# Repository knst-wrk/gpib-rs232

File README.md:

# GPIB-RS232 Converter

This circuit interfaces a GPIB bus to a serial port.

It was originally published on the German website [Mikrocontroller.net](https://www.mikrocontroller.net/articles/GPIB-RS232-Schnittstelle) and [featured on Hackaday](https://hackaday.com/2012/05/01/gpib-connectivity-twofer/).

## License and state

Software is GPL-3.0 unless otherwise noted.

The circuit design is licensed under the CERN OHL-W-2.0.

The project has been sitting around for some time now. I would consider it to be mildly abandoned by now as I currently do not have the time and/or energy to continue working on it, unfortunately. Please feel free to send me a mail if you have questions or suggestions or if you can make use of it.

## GPIB-RS232-Schnittstelle

Viele Messgeräte sind (auch heute immer noch) mit einer GPIB-Schnittstelle ausgerüstet. Zwar handelt es sich hierbei zwar um einen eher antiquierten, parallelen Datenbus, den Hewlett-Packard vor nunmehr vierzig Jahren in die Welt gesetzt hat, dennoch sind es vor allem die [geringen Übertragungslatenzen](https://www.ni.com/en/support/downloads/instrument-drivers/instrument-bus-performance---making-sense-of-competing-bus-techn.html#vergleichsweise), welche die GPIB-Schnittstelle auch weiterhin für zeitkritische Aufgaben prädestinieren. Mittlerweile wurde die GPIB-Schnittstelle vielfach genormt - unter anderem unter der Bezeichnung IEEE488 und IEC-625, daher auch die gängige Bezeichnung als *IEC-BUS*.

Der Bus ist acht Bit breit und beinhaltet neben einer Reihe von Steuerleitungen ein Drei-Leitungs-Handshake. Dieses ist in Wired-And-Methodik ausgeführt, d.h. der Bus wird terminiert und mit Pull-up versehen, welchen die Busteilnehmer dann aktiv nach Masse ziehen können. Das Handshake gewährleistet, dass der Bus nur so schnell betrieben wird, wie das langsamste Gerät am Bus Daten aufnehmen kann. Der genaue Ablauf des Bustransfers ist in dieser Grafik recht anschaulich beschrieben.

Funktionen:
* GPIB-Controller, also SH, AH, C,
* HP Universal Language Interface auf der seriellen,
* Zustandsanzeige über Blinkmuster...,
* Vernünftige Pegelwandler und keine Spannungsteiler,
* umfangreiche End-of-string-Behandlung.

## Terminologie
Sämtliche Signale auf dem Bus sind Low-aktiv.

Der Bus besteht aus den acht Datenleitungen des Datenbus, die das Datenbyte aufnehmen (invertiert, da Low-aktiv). Ein Byte kann *auf den Bus gelegt werden*, indem die Treiber eingeschaltet werden und die Datenleitungen entsprechend gesetzt werden. Um das Byte wieder *vom Bus zu nehmen*, werden die Treiber wieder abgeschaltet. Das ist etwas anderes, als ein Byte *vom Bus zu lesen*!

Dazu kommt der Übergabebus mit den drei Handshakeleitungen DAV (data available), NDAC (no data accepted) und NRFD (not ready for data). Schließlich bilden ein paar Steuerleitungen den Steuerbus; die wichtigsten wären
* ATN (attention),
* REN (remote enable) und
* EOI (end or identify).

Man spricht beim GPIB eigentlich immer von irgendwelchen *Botschaften*, die abgesetzt oder zurückgezogen werden. Es kann sich dabei um Bytes handeln, die über den Bus gehen, oder auch schlicht um eine der Steuer- oder Handshakeleitungen, die einen bestimmten Pegel annimmt. Da der Bus Low-aktiv arbeitet, sind insbesondere die Steuerleitungen aktiv, wenn sie einen niedrigen Spannungspegel annehmen. Die entsprechende Botschaft ist dann *gesendet* (oder *abgesetzt*). Wegen Wired-and können auch mehrere Busteilnehmer eine Botschaft zugleich absetzen. Sie bleibt dann solange abgesetzt, bis sämtliche Teilnehmer sie wieder *zurückgezogen* haben.

Mit der DAV-Botschaft (data valid) wird signalisiert, dass der Datenbus gültige Daten enthält, die nun gelesen werden können. Wird die EOI-Botschaft (end or identify) zusammen mit einem Byte übertragen, so handelt es sich um das letzte Byte einer längeren Nachricht. Die ATN-Botschaft (attention) fordert alle Busteilnehmer auf, sämtliche Bustätigkeit zu unterbrechen und den Datenbus freizugeben (etwaige Talker nehmen ihr Byte vom Bus).

## Hardware
Die Schnittstelle wurde vollständig in bedrahteter Technologie auf einer einseitigen Platine aufgebaut. Für die serielle Schnittstelle kommt der MAX232 zum Einsatz, die Busankopplung nehmen die klassichen SN75160 (Daten) und SN75162 (Steuerleitungen). Zusammengehalten wird beides von einem ATmega16 oder pinkompatiblen. Die Bustreiber sind eigentlich typisch; den -160 bekommt man bei Reichelt. Den zweiten gibt es dort noch als -161; dem fehlen allerdings zwei wichtige Signale, es muss also der -162 sein.

Notfalls lassen sich die Treiber auch aus alten GPIB-Karten ausschlachten...

Zuletzt habe ich noch ein geregeltes Netzteil (7805) spendiert, um die Karte über Hohlstecker zu versorgen. Man halte sich dabei die vergleichsweise große Verlustleistung der Bustreiber vor Augen, wenn man mit dem Gedanken spielt, die Karte über USB zu versorgen: Im Leerlauf insgesamt etwa 150mA.

Zum Bus hin habe ich den typischen Centronics-Stecker (*micro ribbon connector*) verbaut. Da ist etwas Vorsicht geboten, denn die gibt es auch in gespiegelter Bauform. Der Stecker ist trapezförmig; die normale Bauform hat das schmale Ende unten (Richtung Platine), die gespiegelte Version nach oben. Ich habe die normale Version gewählt.

Es gibt auf der Platine keine diskrete Logik für die ATN-Leitung. Das mag mancheinem vielleicht schon aufgefallen sein, der alte GPIB-PCI-Steckkarten gesehen hat -- die glichen anfangs einem TTL-Grab. Hintergrund ist, dass in der Spezifikation ein recht zeitkritisches Verhalten als Antwort auf die ATN-Botschaft vereinbart ist. Nämlich haben alle Busteilnehmer bei Empfang der ATN-Botschaft ihren Busbetrieb binnen 200ns einzustellen und die Treiber zu deaktivieren.

Das Zeitfenster von 200ns ist recht sportlich, um es mit einem Interrupt aufzufangen, gerade bei den alten Mikroprozessors, die auf den Steckkarten verbaut wurden, und auch für den AVR. Daher hat man diese Spezifikation (und noch ein paar weitere) mit diskreter Logik erschlagen. Diese hat sich dann schnell um die Bustreiber gekümmert und einfach ein Flipflop gesetzt. Dieses hat der Mikroprozessor dann bei nächster Gelegenheit abgeholt und hatte damit wieder genug Zeit, zu reagieren.

## Software
Die Software ist in C für avr-gcc geschrieben.

### Controller-Betrieb
Die fehlende diskrete Logik hat zur Konsequenz, dass die Schnittstelle eigentlich nur als Controller standardkonform funktioniert. Denn nur dann kümmert sie sich selbst um die ATN-Botschaft und muss demnach nicht auf fremde ATN-Botschaften reagieren, was sie ja aus Zeitgründen nicht innerhalb des spezifizierten Zeitfensters kann. Würde man die Schnittstelle nur als Sprecher (Talker) betreiben, könnte der momentane Controller die ATN-Botschaft versenden und gleich darauf ein paar Daten auf den Bus legen. Tut er das so schnell wie möglich, also nach 200ns, hätte die Schnittstelle keine Chance, etwaige Daten vom Bus zu nehmen, denn mit zwei Prozessorzyklen des AVR (bei 8MHz) wären die 200ns schon beim Sprung in den Interrupt verstrichen (rjmp mit zwei Zyklen = 250ns). Und da sind noch nicht die vier Takte drin, die bis zum Interruptvektor vergehen, denn es muss ja noch der Programmzähler auf den Stack gelegt werden.

Praktisch ist der Bus in Wired-and ausgeführt, d.h. es entstehen zumindest keine Kurzschlüsse, wenn zwei gleichzeitig reden, weil die Treiber nicht schnell genug abgeschaltet werden. Es können aber Daten kaputt gehen, wenn andere Teilnehmer die Daten früher vom Bus lesen, als jemand anderes seine Treiber abschaltet. Und zwar nach folgendem Szenario:

* Wir legen ein Byte auf den Bus und
* signalisieren das mit der DAV-Botschaft.
* Ein paar Hörer lesen das Byte vom Bus.
* Der Controller setzt die ATN-Botschaft ab,
* er wartet die 200ns und
* legt seinerseits ein Byte auf den Bus (dieses kollidiert mit unserem) und
* signalisiert das mit der DAV-Botschaft. Die DAV-Botschaft bleibt also bestehen (Wired-and).
* Ein paar andere Hörer lesen das (kaputte) Byte vom Bus.
* Wir bemerken die ATN-Botschaft und ziehen Byte und ATN-Botschaft zurück.
* Wegen Wired-and ist die DAV-Botschaft noch immer aktiv.
* ...

Der Betrieb als Hörer leidet am gleichen Problem, hier ist allerdings das Lesen vom Bus kritisch. Ein Sprecher könnte ein Datenbyte auf den Bus legen und dies mit der DAV-Botschaft signalisieren. Das bemerken wir und beginnen mit dem Lesevorgang (Interrupt betreten und so weiter). Indes unterbricht ein Controller die Übertragung mit der ATN-Botschaft der Bus enthält dann ungültige Daten. Und wir fahren munter mit dem begonnenen Lesevorgang fort...

Unterm Strich: Meistens funktioniert es.

### Protokoll
Für das Protokoll über die serielle Schnittstelle habe ich mich vom Universal Language Interface (ULI) von Hewlett-Packard inspirieren lassen. Das Heftchen von 1993 fiel mir zufällig in die Hände und ich fand das ganz passend.

Das Prinzip dahinter ist recht einfach. Früher hat man eine GPIB-Karte in den Computer gesteckt und bekam einen Treiber für ein recht bekanntes Betriebssystem seiner Zeit. Dazu kamen ein paar Bibliotheken für BASIC, C, Pascal und so weiter, die entsprechende Funktionen boten. Dazu gehörten Lese- und Schreibbefehle `ibrd()` und `ibwr()`, Funktionen zur Adressiereung und allerlei Zubehör. Je nach Hersteller waren diese Funktionen dann mehr oder weniger ähnlich und/oder inkompatibel.

Beim ULI dagegen erzeugte der Treiber quasi eine Gerätedatei, die man in der jeweiligen Programmiersprache dann mit Standard-E/A öffnen konnte. Das entspricht in etwa dem, was sich unter *nix schon länger bewährt hat. Eine Bibliothek gibt es nicht mehr, stattdessen werden Befehle zeilenweise in dieses Gerät geschrieben und Antworten kommen zeilenweise wieder heraus.

Zeilenweise ist in diesem Zusammenhang schwierig. Einerseits könnten Zeilenendzeichen (Wagenrücklauf CR, Zeilenvorschub LF) auch im Nutzdatenstrom vorkommen, andererseits konstruierte sich anfangs jeder Hersteller von GPIB-Messgeräten ein eigenes Bild vom Zeilenende. Manche wollten nur ein CR oder LF, manche CRLF, ein Semikolon oder die EOI-Botschaft (die EOI-Steuerleitung kann zusammen mit dem letzten übertragenen Byte gesetzt werden und signalisiert dann das Zeilenende). Glücklicherweise waren und sind die meisten Geräte recht tolerant und akzeptieren eine Vielzahl dieser Möglichkeiten, wenn man mit ihnen spricht. Tragischerweise antworten sie aber auch mit einer Vielzahl dieser Möglichkeiten, wenn sie umgekehrt mit uns sprechen...

### Architektur
Die Firmware ist mehrschichtig konstruiert. Ganz unten liegen zwei Ringpuffer, einer für die serielle Schnittstelle und einer für den GPIB. Diese Puffer kümmern sich um die Handshakes (Dreileitung für GPIB und RTS/CTS für die serielle).

Darüber liegt eine Strom-Schicht (Strom von Datenstrom), die aus den eingehenden Datenströmen der Ringpuffer die Zeilenenden herausfischt und die Zeilenenden in den ausgehenden Strömen erzeugt. Von da an sind beide Schnittstellen an die C-Laufzeitbibliothek angeschlossen, sodass die Kommunikation in weiten Teilen wie gewohnt mit `puts()`/`printf()`/... abläuft. Die Zeilenenden in den Eingangsströmen werden dabei als End-of-file (EOF) dargestellt. Da man allerdings kein EOF in den Ausgangsströmen erzeugen kann (könnte man schon, mit `fclose()`; diese Funktion ist aber schon anderweitig vergeben), werden die Zeilenenden mit einem flush ausgelöst. Blöderweise ist auch `fflush()` schon vergeben, daher zwei spezifische Routinen.

Obenauf liegt ein Terminal und verbindet die beiden Schnittstellen über das ULI.

### Beispiel
Eine Sitzung mit dem Universalzähler *PM6652* und dem Generator *PM5192* könnte etwa so aussehen:

Die Baudrate wird automatisch am ersten empfangenen Zeilenvorschub ermittelt:

    $ echo > ttyUSB1

Schnittstelle einschalten und den Zähler (Adresse 14) parametrieren:

    $ echo "ONLINE" > ttyUSB1
    $ echo "REMOTE 14" > ttyUSB1
    $ echo "OUTPUT 14;D" > ttyUSB1
    $ echo "OUTPUT;F1TE1G0SM5" > ttyUSB1

Zähler auf 1337Hz einstellen:

    $ echo "REMOTE 15" > ttyUSB1
    $ echo "OUTPUT 15;OUT 15;WSLA4F1337" > ttyUSB1

Messung durchführen und Ergebnis abholen:

    $ echo "TRIGGER 14" > ttyUSB1
    $ echo "ENTER 14" > ttyUSB1
    $ line < ttyUSB1
    FA 001.3370011E+3

Die Anführungszeichen sind nötig, damit die Shell das Semikolon nicht als Befehlsende interpretiert.

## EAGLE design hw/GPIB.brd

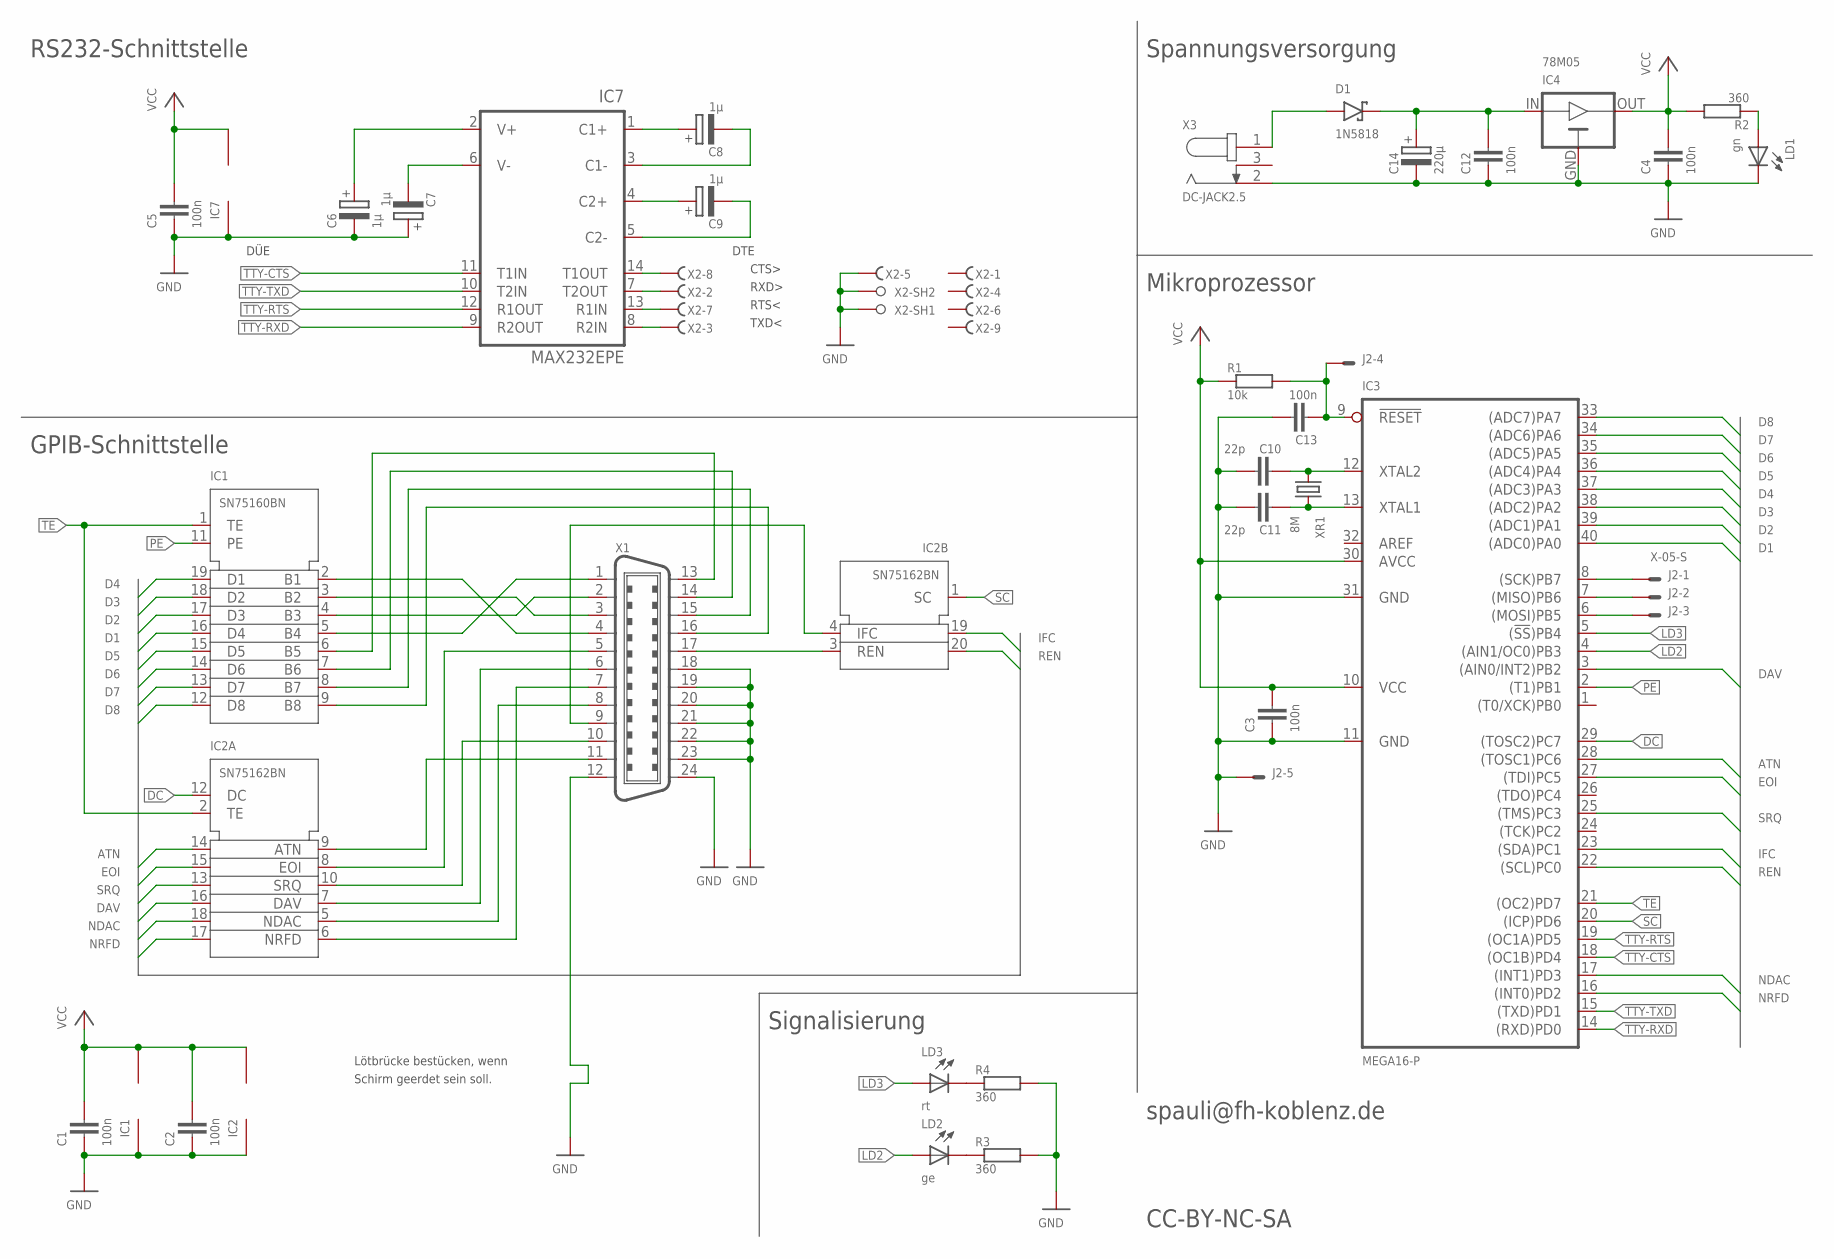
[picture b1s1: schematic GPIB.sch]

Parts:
C1, C2, C3, C4, C5, C12, C13: 100n; 024X044/020
C6, C7, C8, C9: 1µ; POL-D040/008
C10, C11: 22p; 024X044/010
C14: 220µ; POL-D080/014
D1: 1N5818; DO41/40
IC1: SN75160BN; DIL20
IC2: SN75162BN; DIL22-04
IC3: MEGA16-P; DIL40
IC4: 78M05; 78*-TO220-L
IC7: MAX232EPE; DIL16
J2: X-05-S; 05/4X010-S
LD1: gn; LED3MM
LD2: ge; LED3MM
LD3: rt; LED3MM
R1: 10k; 0204/030
R2, R3, R4: 360; 0204/030
X1: C24H; 24H
X2: 09F; F09HP
X3: DC-JACK2.5; DC-2.5
XR1: 8M; HC49-S

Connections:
!RESET: C13.2, IC3.9 (!RESET), J2.4, R1.2
ATN: IC2.14 (ATN_), IC3.28 ((TOSC1)PC6)
D1: IC1.16 (D4), IC3.40 ((ADC0)PA0)
D2: IC1.17 (D3), IC3.39 ((ADC1)PA1)
D3: IC1.18 (D2), IC3.38 ((ADC2)PA2)
D4: IC1.19 (D1), IC3.37 ((ADC3)PA3)
D5: IC1.15 (D5), IC3.36 ((ADC4)PA4)
D6: IC1.14 (D6), IC3.35 ((ADC5)PA5)
D7: IC1.13 (D7), IC3.34 ((ADC6)PA6)
D8: IC1.12 (D8), IC3.33 ((ADC7)PA7)
DAV: IC2.16 (DAV_), IC3.3 ((AIN0/INT2)PB2)
DC: IC2.12 (DC), IC3.29 ((TOSC2)PC7)
EOI: IC2.15 (EOI_), IC3.27 ((TDI)PC5)
GND: C1.2, C2.2, C3.2, C4.2, C5.2, C6.-, C7.+, C10.1, C11.1, C12.2, C13.1, C14.-, IC1.10 (GND), IC2.11 (GND), IC3.11 (GND), IC3.31 (GND), IC4.GND, IC7.15 (GND), J2.5, LD1.K (C), R3.2, R4.2, X1.12, X1.18, X1.19, X1.20, X1.21, X1.22, X1.23, X1.24, X2.5 (F), X2.SH1 (-SH), X2.SH2 (-SH), X3.2 (GROUND)
IFC: IC2.19 (IFC_), IC3.23 ((SDA)PC1)
LD2: IC3.4 ((AIN1/OC0)PB3), LD2.A
LD3: IC3.5 ((!SS!)PB4), LD3.A
MISO: IC3.7 ((MISO)PB6), J2.2
MOSI: IC3.6 ((MOSI)PB5), J2.3
unnamed: C8.+, IC7.1 (C1+)
unnamed: C9.+, IC7.4 (C2+)
unnamed: C9.-, IC7.5 (C2-)
unnamed: C8.-, IC7.3 (C1-)
unnamed: C6.+, IC7.2 (V+)
unnamed: IC1.2 (B1), X1.4
unnamed: C7.-, IC7.6 (V-)
unnamed: IC1.3 (B2), X1.3
unnamed: IC1.4 (B3), X1.2
unnamed: IC1.5 (B4), X1.1
unnamed: IC1.6 (B5), X1.13
unnamed: IC1.7 (B6), X1.14
unnamed: IC1.8 (B7), X1.15
unnamed: IC1.9 (B8), X1.16
unnamed: IC2.8 (EOI), X1.5
unnamed: IC2.7 (DAV), X1.6
unnamed: IC2.6 (NRFD), X1.7
unnamed: IC2.5 (NDAC), X1.8
unnamed: IC2.10 (SRQ), X1.10
unnamed: IC2.9 (ATN), X1.11
unnamed: IC2.3 (REN), X1.17
unnamed: IC2.4 (IFC), X1.9
unnamed: C10.2, IC3.12 (XTAL2), XR1.1
unnamed: C11.2, IC3.13 (XTAL1), XR1.2
unnamed: D1.A, X3.1 (LIVE)
unnamed: C12.1, C14.+, D1.C, IC4.IN
unnamed: LD1.A, R2.1
unnamed: LD3.K (C), R4.1
unnamed: LD2.K (C), R3.1
unnamed: IC7.8 (R2IN), X2.3 (F)
unnamed: IC7.13 (R1IN), X2.7 (F)
unnamed: IC7.14 (T1OUT), X2.8 (F)
unnamed: IC7.7 (T2OUT), X2.2 (F)
NDAC: IC2.18 (NDAC_), IC3.17 ((INT1)PD3)
NRFD: IC2.17 (NRFD_), IC3.16 ((INT0)PD2)
PE: IC1.11 (PE), IC3.2 ((T1)PB1)
REN: IC2.20 (REN_), IC3.22 ((SCL)PC0)
SC: IC2.1 (SC), IC3.20 ((ICP)PD6)
SCK: IC3.8 ((SCK)PB7), J2.1
SRQ: IC2.13 (SRQ_), IC3.25 ((TMS)PC3)
TE: IC1.1 (TE), IC2.2 (TE), IC3.21 ((OC2)PD7)
TTY-CTS: IC3.18 ((OC1B)PD4), IC7.11 (T1IN)
TTY-RTS: IC3.19 ((OC1A)PD5), IC7.12 (R1OUT)
TTY-RXD: IC3.14 ((RXD)PD0), IC7.9 (R2OUT)
TTY-TXD: IC3.15 ((TXD)PD1), IC7.10 (T2IN)
VCC: C1.1, C2.1, C3.1, C4.1, C5.1, IC1.20 (VCC), IC2.22 (VCC), IC3.10 (VCC), IC3.30 (AVCC), IC4.OUT, IC7.16 (VCC), R1.1, R2.2

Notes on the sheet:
RS232-Schnittstelle
TXD<
RTS<
RXD>
CTS>
DTE
DÜE
GPIB-Schnittstelle
Spannungsversorgung
Lötbrücke bestücken, wenn
Schirm geerdet sein soll.
Mikroprozessor
spauli@fh-koblenz.de
Signalisierung
CC-BY-NC-SA

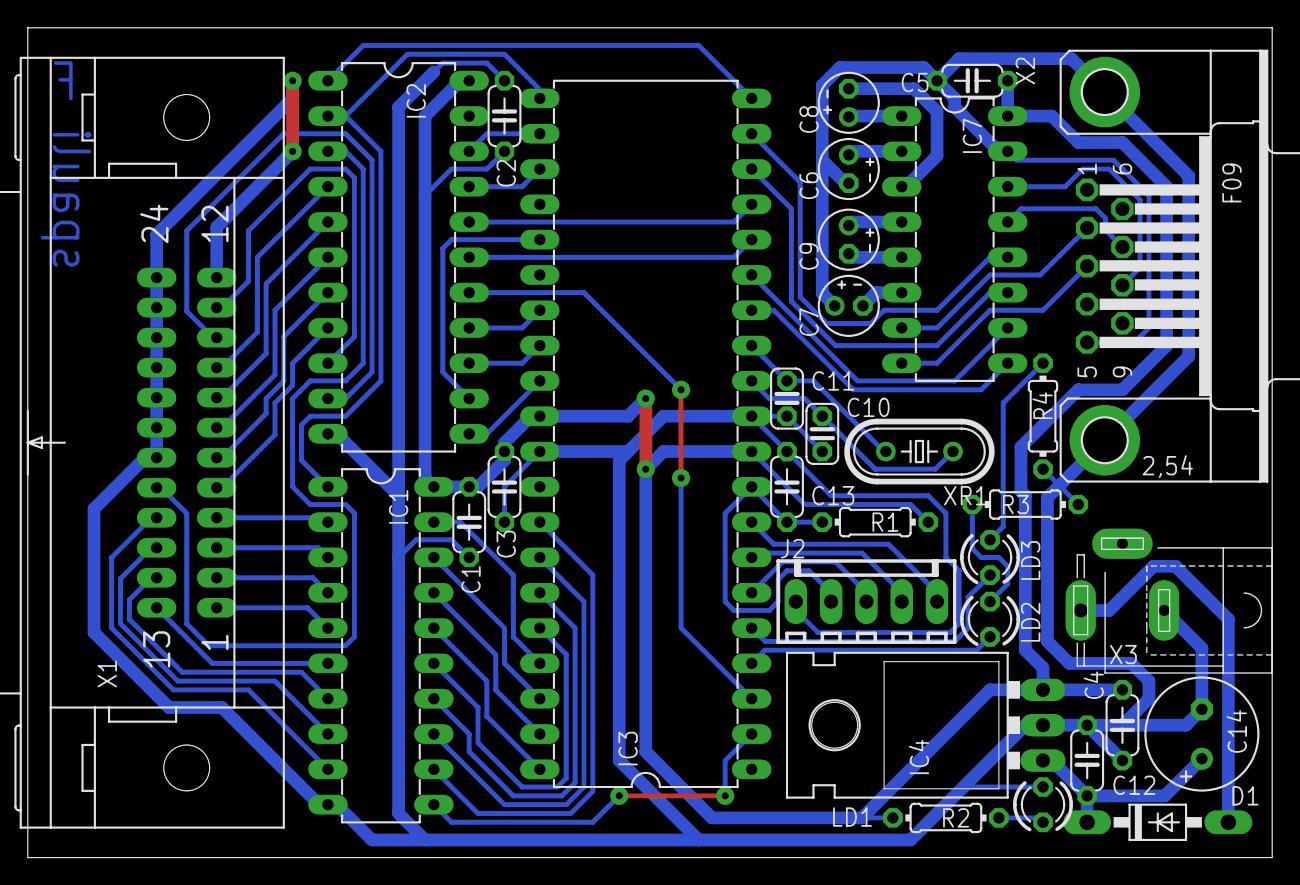
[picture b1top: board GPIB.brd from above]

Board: 2 copper layers, 89.5 x 59.7 mm, 32 parts (0 on the bottom side), 65 nets.

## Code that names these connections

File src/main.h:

/* GPIB to RS232 converter.
Copyright (C) 2012  Sven Pauli <sven_pauli@gmx.de>

This program is free software: you can redistribute it and/or
modify it under the terms of the GNU General Public License as
published by the Free Software Foundation, either version 3 of
the License, or (at your option) any later version.

This program is distributed in the hope that it will be useful,
but WITHOUT ANY WARRANTY; without even the implied warranty of
MERCHANTABILITY or FITNESS FOR A PARTICULAR PURPOSE. See the
GNU General Public License for more details.

You should have received a copy of the GNU General Public License
along with this program. If not, see
	<http://www.gnu.org/licenses/>. */


#ifndef MAIN_H
#define MAIN_H

/*
	PA0		Data 1
	  1		Data 2
	  2		Data 3
	  3		Data 4
	  4		Data 5
	  5		Data 6
	  6		Data 7
	  7		Data 8

	PB0
	  1	PE
	  2		DAV
	  3	LD2
	  4	LD3
	  5	MOSI
	  6	MISO
	  7	SCK

	PC0		REN
	  1		IFC
	  2
	  3		SRQ
	  4
	  5		EOI
	  6		ATN
	  7	DC

	PD0	RxD
	  1	TxD
	  2		NRFD
	  3		NDAC
	  4	CTS
	  5	RTS
	  6	SC
	  7	TE
*/

#include "io.h"

#define YELLOW		BITWISE_CHAR(PORTB, PB3)
#define RED		BITWISE_CHAR(PORTB, PB4)



#ifdef DEBUG

#include <stdio.h>
#define ERROR(e) \
	do {								\
		printf("ERROR (%u) %s:%u\n", e,__FILE__, __LINE__);	\
		red_pattern = (e);					\
	} while (0)

#else

#define ERROR(e) \
	do { red_pattern = (e); } while (0)

#endif

#define STATUS(s) \
	do { yellow_pattern = (s); } while (0)


/* Error indicator */
#define NO_ERROR			0x0
#define TTY_TRANSMISSION_ERROR		0xFFFE
#define TTY_OVERFLOW_ERROR		0xAAAA
#define GPIB_TIMEOUT_ERROR		0xFFFF
#define GPIB_TRANSMISSION_ERROR		0xFEFE
#define GPIB_OVERFLOW_ERROR		0x00AA
#define TERMINAL_ERROR			0x0001

/* Status indicator */
#define NO_STATUS			0x0
#define OFFLINE_STATUS			NO_STATUS
#define ONLINE_STATUS			0x0001
#define RECEIVE_STATUS			0x00FF
#define RECEIVING_STATUS		0x00AA
#define TRANSMIT_STATUS			0x0F0F
#define TRANSMITTING_STATUS		0x0A0A


extern unsigned red_pattern;
extern unsigned yellow_pattern;

#endif

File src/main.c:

/* GPIB to RS232 converter.
Copyright (C) 2012  Sven Pauli <sven_pauli@gmx.de>

This program is free software: you can redistribute it and/or
modify it under the terms of the GNU General Public License as
published by the Free Software Foundation, either version 3 of
the License, or (at your option) any later version.

This program is distributed in the hope that it will be useful,
but WITHOUT ANY WARRANTY; without even the implied warranty of
MERCHANTABILITY or FITNESS FOR A PARTICULAR PURPOSE. See the
GNU General Public License for more details.

You should have received a copy of the GNU General Public License
along with this program. If not, see
	<http://www.gnu.org/licenses/>. */


#include <avr/io.h>
#include <avr/interrupt.h>

#include "gpib.h"
#include "tty.h"
#include "io.h"
#include "configuration.h"
#include "terminal.h"
#include "streams.h"
#include "main.h"

unsigned red_pattern;
unsigned yellow_pattern;


static INLINE(void pattern(void)) {
	static unsigned current_red_pattern = 0;
	static unsigned current_yellow_pattern = 0;

	static unsigned char position = 0;
	if (++position >= 16) {
		/* Wrap */
		position = 0;
		current_red_pattern = red_pattern;
		current_yellow_pattern = yellow_pattern;
	}

	RED = current_red_pattern & 0x1;
	current_red_pattern >>= 1;

	YELLOW = current_yellow_pattern & 0x1;
	current_yellow_pattern >>= 1;
}

ISR(TIMER0_COMP_vect) {
	static unsigned char postscaler = 0;
	if (postscaler++ >= 8) {
		/* 128ms interrupt */
		postscaler = 0;

		pattern();
	}

	/* 16ms interrupt */
	gpib_timer();
}

int main(void) {
	/* 16ms interrupt */
	OCR0 = 125;
	TCCR0 =
		_BV(WGM01) |
		_BV(CS02) |
		_BV(CS00);
	TIMSK |= _BV(OCIE0);


	YELLOW = 1;
	RED = 0;

	DDRB |=
		_BV(PB3) |
		_BV(PB4) |
		_BV(PB5) |
		_BV(PB7);

	DDRB &= ~_BV(6);

	gpib_prepare();
	configuration_prepare();
	tty_prepare();

	streams_prepare();
	terminal_prepare();
	sei();

	for (;;)
		terminal();
}

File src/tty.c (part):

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
/* TODO implement CTS handshake */

#define RTS		BITWISE_CHAR(PIND, PD5)
#define CTS		BITWISE_CHAR(PORTD, PD4)

/* USART circular buffers.
Data to be transmitted is enclosed by the head and tail indexes:
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void tty_prepare(void) {
	/* Transmitter disabled, inactive state */
	CTS = 0;
	PORTD |= _BV(PD1);
	DDRD |= _BV(PD1);
	DDRD &= ~( _BV(PD0) | _BV(PD5) );

	/* Detect initial baudrate */
	unsigned baud;
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
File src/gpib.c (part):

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#include "gpib.h"

/* High is terminated */
#define _PE					BITWISE_CHAR(PORTB, PB1)

/* Low is controller */
#define _DC					BITWISE_CHAR(PORTC, PC7)

/* High is controller */
#define _SC					BITWISE_CHAR(PORTD, PD6)

/* High is talking */
#define _TE					BITWISE_CHAR(PORTD, PD7)


/* Control bus lines */
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	direction = 0;
	DEASSERT(IBNDAC);

	DDRB |= _BV(PB1);

	DDRC |= _BV(PC7);
	DDRD |=
		_BV(PD6) |
		_BV(PD7);

	MCUCR |=
		_BV(ISC11) |
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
